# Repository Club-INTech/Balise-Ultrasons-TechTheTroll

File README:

Ceci est le dépôt de la balise de l'équipe TechTheTroll, conçue par Sylvain

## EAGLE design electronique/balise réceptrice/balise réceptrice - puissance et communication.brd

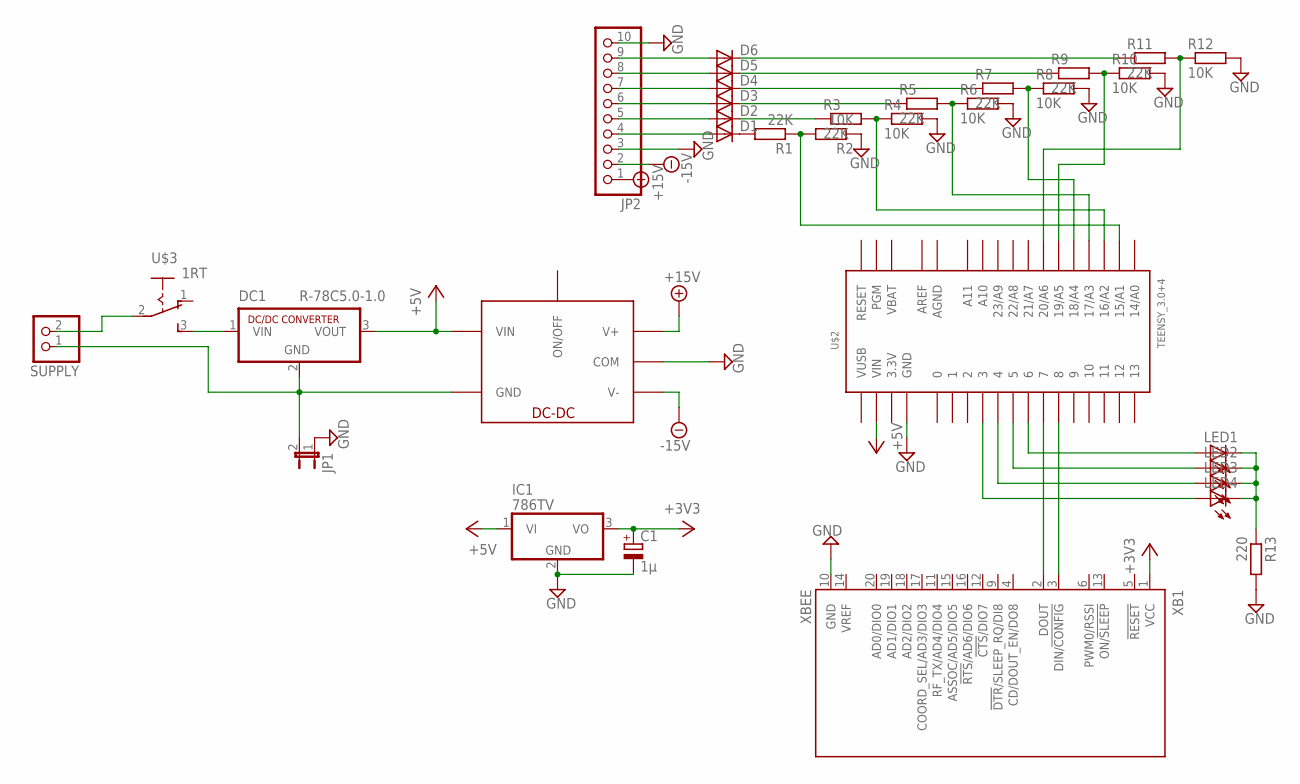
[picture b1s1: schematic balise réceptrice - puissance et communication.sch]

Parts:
C1: 1µ; E2,5-6E
D1, D2, D3, D4, D5, D6: DIODE-D-2.5; D-2.5
DC1: R-78C5.0-1.0; SIP3
IC1: 786TV; TO220V
JP1: JP1E; JP1
JP2: PINHD-1X10; 1X10
LED1, LED2, LED3, LED4: LED3MM
R1, R3, R5, R7, R9, R11: 22K; 0204/7
R2, R4, R6, R8, R10, R12: 10K; 0207/2V
R13: 220; 0204/7
SUPPLY: PINHD-1X2; 1X02
U$1: TMR-6-0523; 7SIL
U$2: TEENSY_3.0+4
U$3: 1RT
XB1: XBEE

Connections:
3.3V: U$2.3.3V, U$2.3.3V1 (3.3V)
+3V3: C1.+, IC1.3 (VO), XB1.1 (VCC)
+5V: DC1.3 (VOUT), IC1.1 (VI), U$1.VCC (VIN), U$2.VIN
+15V: JP2.1, U$1.+V (V+)
-15V: JP2.2, U$1.-V (V-)
AGND: U$2.AGND
AREF: U$2.AREF
GND: C1.-, IC1.2 (GND), JP1.1, JP2.3, JP2.10, R2.1, R4.2, R6.2, R8.2, R10.2, R12.2, R13.2, U$1.COM, U$2.GND, U$2.GND1 (GND), XB1.10 (GND)
unnamed: DC1.2 (GND), JP1.2, SUPPLY.1, U$1.GND
unnamed: D1.A, JP2.4
unnamed: U$2.7, XB1.2 (DOUT)
unnamed: U$2.8, XB1.3 (DIN/!CONFIG)
unnamed: D2.A, JP2.5
unnamed: D3.A, JP2.6
unnamed: D4.A, JP2.7
unnamed: D5.A, JP2.8
unnamed: D6.A, JP2.9
unnamed: R1.1, R2.2, U$2.15/A1
unnamed: D1.C, R1.2
unnamed: D2.C, R3.1
unnamed: R3.2, R4.1, U$2.16/A2
unnamed: D3.C, R5.1
unnamed: R5.2, R6.1, U$2.17/A3
unnamed: D4.C, R7.1
unnamed: R7.2, R8.1, U$2.18/A4
unnamed: D5.C, R9.1
unnamed: R9.2, R10.1, U$2.19/A5
unnamed: D6.C, R11.1
unnamed: R11.2, R12.1, U$2.20/A6
unnamed: DC1.1 (VIN), U$3.3 (S)
unnamed: LED1.A, U$2.6
unnamed: LED2.A, U$2.5
unnamed: LED3.A, U$2.4
unnamed: LED4.A, U$2.3
unnamed: LED1.K (C), LED2.K (C), LED3.K (C), LED4.K (C), R13.1
unnamed: SUPPLY.2, U$3.2
VBAT: U$2.VBAT
VUSB: U$2.VUSB

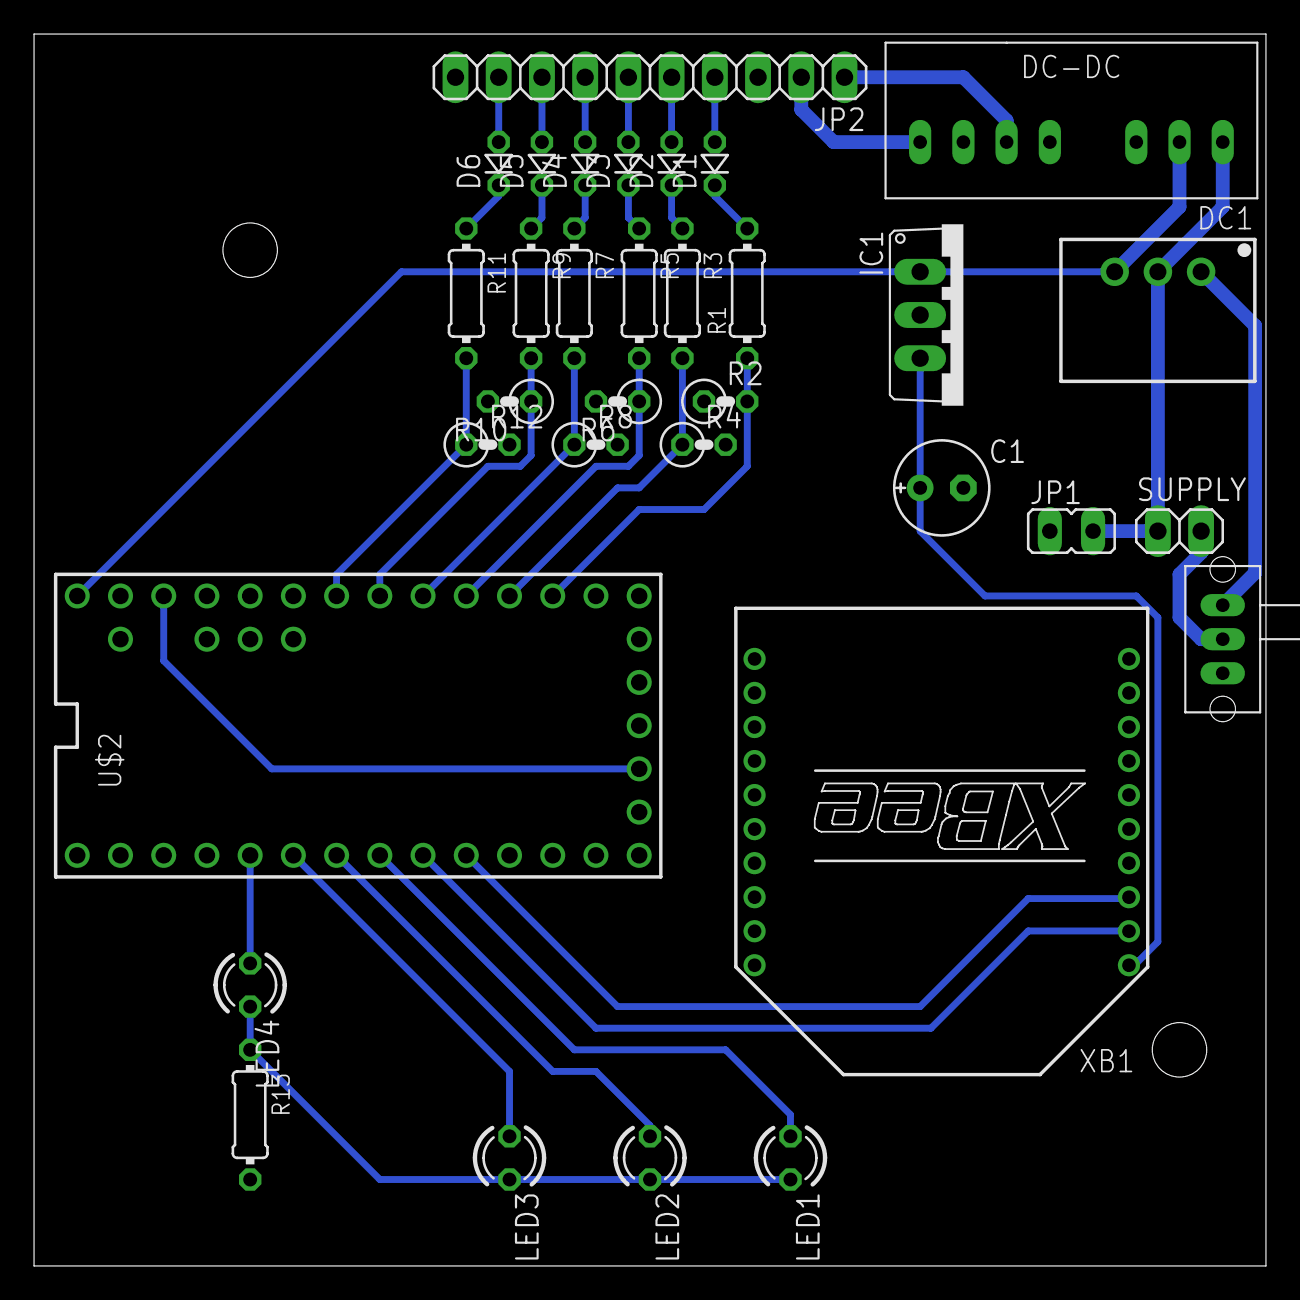
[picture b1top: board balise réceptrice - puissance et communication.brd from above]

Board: 2 copper layers, 72.4 x 72.4 mm, 33 parts (0 on the bottom side), 34 nets.

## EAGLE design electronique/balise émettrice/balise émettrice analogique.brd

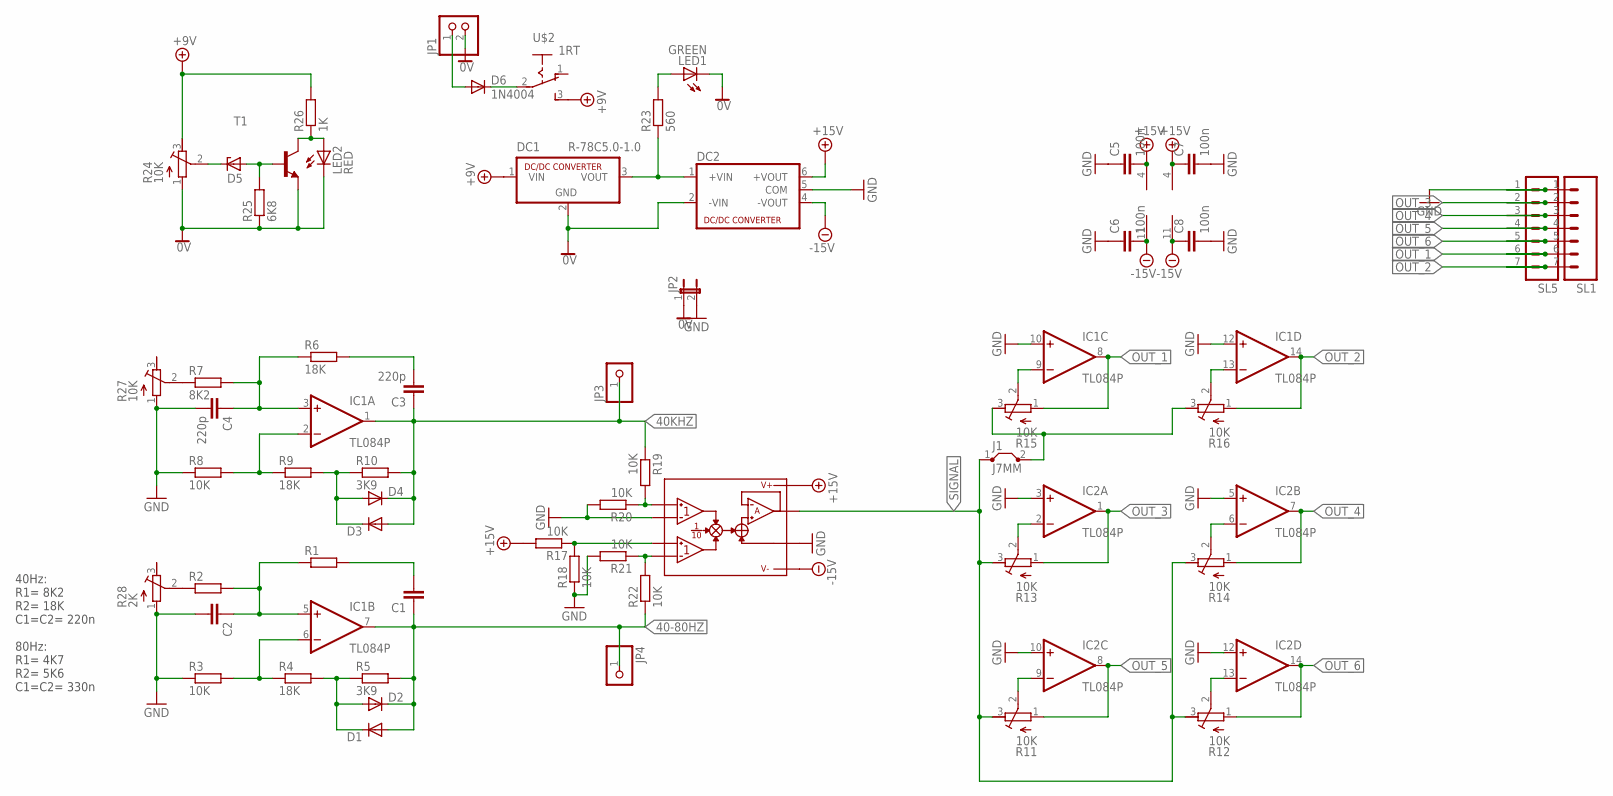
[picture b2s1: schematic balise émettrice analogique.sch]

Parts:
C1, C2: C-EU075-032X103; C075-032X103
C3, C4: 220p; C075-032X103; MPN EEE1EA220SP
C5, C6, C7, C8: 100n; C050-024X044
D1, D2, D3, D4: DIODE-D-2.5; D-2.5
D5: ZENER-DIODEZD-2.5; ZDIO-2.5
D6: 1N4004; DO41-10
DC1: R-78C5.0-1.0; SIP3
DC2: NMA; MPN NMA1205DC
IC1, IC2: TL084P; DIL14
J1: J7MM; 07
JP1: PINHD-1X2; 1X02
JP2: JP1E; JP1
JP3, JP4: PINHD-1X1; 1X01
LED1: GREEN; Q62902-B155
LED2: RED; Q62902-B155
R1: R-EU_0207/2V; 0207/2V
R2: R-EU_0204/7; 0204/7
R3, R8, R17, R18, R19, R20, R21, R22: 10K; 0207/2V
R4, R6, R9: 18K; 0207/2V
R5, R10: 3K9; 0207/2V
R7: 8K2; 0207/2V
R11, R12, R13, R14, R15, R16, R24, R27: 10K; RTRIM3339P
R23: 560; 0204/7
R25: 6K8; 0207/2V
R26: 1K; 0207/2V
R28: 2K; RTRIM3339P
SL1, SL5: M07; 07P
T1: 2N5400-NPN-TO92-CBE; TO92-CBE
U$1: AD633JN; DIL08
U$2: 1RT

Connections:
0V: DC1.2 (GND), DC2.2 (-VIN), JP1.2, JP2.1, LED1.K (C), LED2.K (C), R24.1 (E), R25.1, T1.E
40-80HZ: C1.1, D1.A, D2.C, IC1.7 (OUT), JP4.1, R5.2, R22.1
40KHZ: C3.1, D3.A, D4.C, IC1.1 (OUT), JP3.1, R10.2, R19.1
+9V: DC1.1 (VIN), R24.3 (A), R26.2, U$2.3 (S)
+15V: C5.2, C7.1, DC2.6 (+VOUT), IC1.4 (V+), IC2.4 (V+), R17.2, U$1.8 (+V)
-15V: C6.2, C8.1, DC2.4 (-VOUT), IC1.11 (V-), IC2.11 (V-), U$1.5 (-V)
GND: C2.2, C4.2, C5.1, C6.1, C7.2, C8.2, DC2.5 (COM), IC1.10 (+IN), IC1.12 (+IN), IC2.3 (+IN), IC2.5 (+IN), IC2.10 (+IN), IC2.12 (+IN), JP2.2, R3.1, R8.1, R18.1, R20.2, R21.2, R27.1 (E), R28.1 (E), SL1.1, SL5.1, U$1.2 (X2), U$1.6 (Z)
unnamed: IC1.6 (-IN), R3.2, R4.1
unnamed: D1.C, D2.A, R4.2, R5.1
unnamed: IC2.9 (-IN), R11.2 (S)
unnamed: C1.2, R1.2
unnamed: C2.1, IC1.5 (+IN), R1.1, R2.2
unnamed: IC1.2 (-IN), R8.2, R9.1
unnamed: D3.C, D4.A, R9.2, R10.1
unnamed: R17.1, R18.2, U$1.3 (Y1)
unnamed: C3.2, R6.2
unnamed: C4.1, IC1.3 (+IN), R6.1, R7.2
unnamed: DC1.3 (VOUT), DC2.1 (+VIN), R23.1
unnamed: IC2.13 (-IN), R12.2 (S)
unnamed: R19.2, R20.1, U$1.1 (X1)
unnamed: LED1.A, R23.2
unnamed: IC2.2 (-IN), R13.2 (S)
unnamed: R21.1, R22.2, U$1.4 (Y2)
unnamed: D5.C, R24.2 (S)
unnamed: IC2.6 (-IN), R14.2 (S)
unnamed: D5.A, R25.2, T1.B
unnamed: D6.A, JP1.1
unnamed: IC1.9 (-IN), R15.2 (S)
unnamed: LED2.A, R26.1, T1.C
unnamed: D6.C, U$2.2
unnamed: IC1.13 (-IN), R16.2 (S)
unnamed: J1.2, R15.3 (A), R16.3 (A)
unnamed: R7.1, R27.2 (S)
unnamed: R2.1, R28.2 (S)
OUT_1: IC1.8 (OUT), R15.1 (E), SL1.6, SL5.6
OUT_2: IC1.14 (OUT), R16.1 (E), SL1.7, SL5.7
OUT_3: IC2.1 (OUT), R13.1 (E), SL1.2, SL5.2
OUT_4: IC2.7 (OUT), R14.1 (E), SL1.3, SL5.3
OUT_5: IC2.8 (OUT), R11.1 (E), SL1.4, SL5.4
OUT_6: IC2.14 (OUT), R12.1 (E), SL1.5, SL5.5
SIGNAL: J1.1, R11.3 (A), R12.3 (A), R13.3 (A), R14.3 (A), U$1.7 (W)

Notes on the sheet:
40Hz: R1= 8K2 R2= 18K C1=C2= 220n 80Hz: R1= 4K7 R2= 5K6 C1=C2= 330n

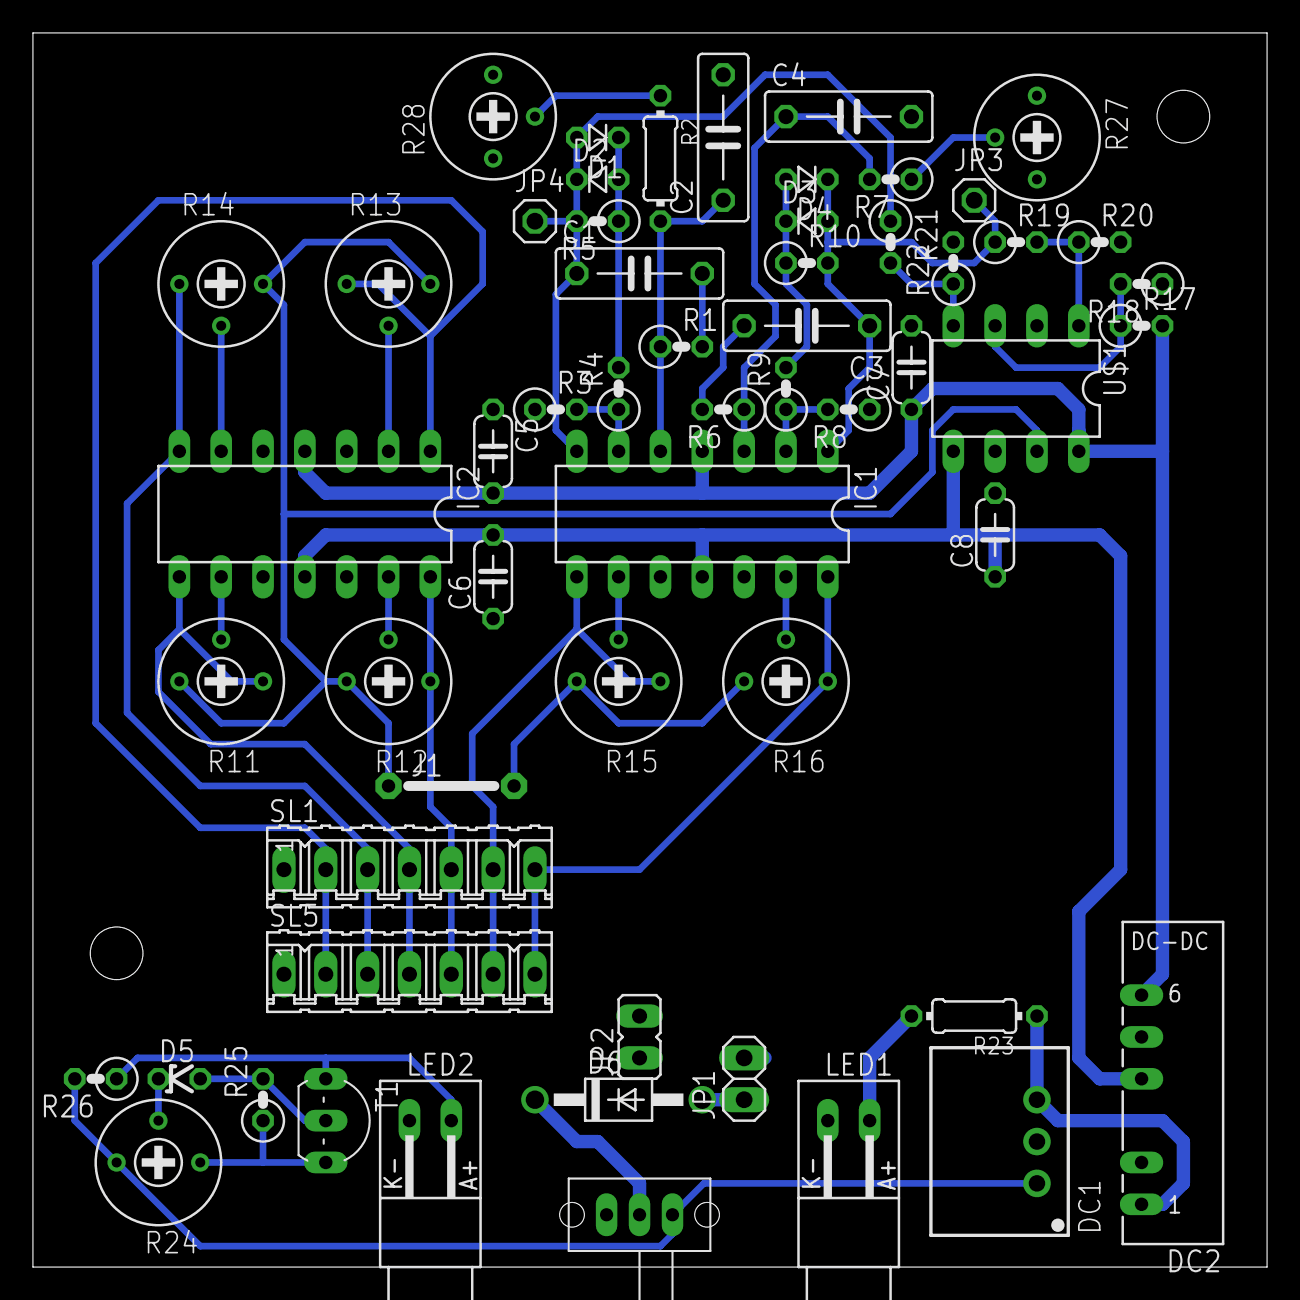
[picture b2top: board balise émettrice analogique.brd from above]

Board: 2 copper layers, 74.9 x 74.9 mm, 58 parts (0 on the bottom side), 41 nets.

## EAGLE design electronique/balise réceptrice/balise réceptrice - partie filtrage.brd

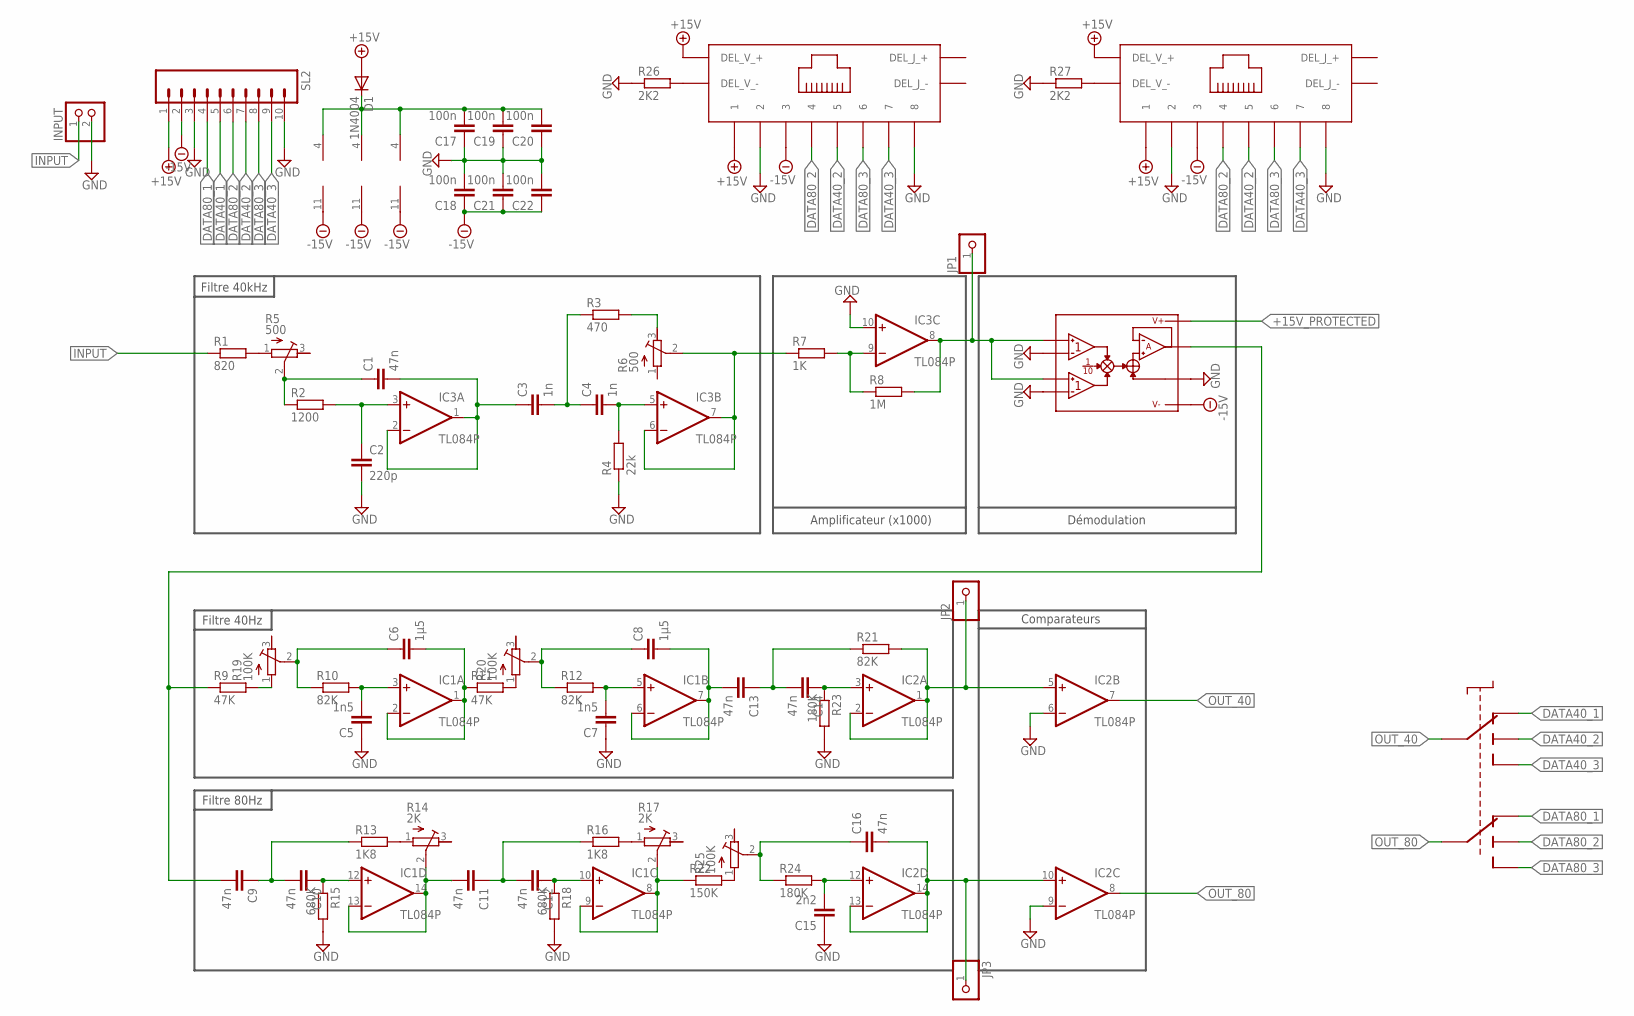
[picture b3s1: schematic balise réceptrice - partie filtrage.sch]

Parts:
C1, C9, C10, C11, C12, C13, C14, C16: 47n; C050-024X044
C2: 220p; C050-024X044; MPN RR1220P-104-B-T5
C3, C4: 1n; C050-024X044
C5, C7: 1n5; C050-024X044
C6, C8: 1µ5; C150-091X182
C15: 2n2; C050-024X044
C17, C18, C19, C20, C21, C22: 100n; C050-024X044
D1: 1N4004; DO41-10
IC1, IC2, IC3: TL084P; DIL14
INPUT: PINHD-1X2; 1X02
JP1, JP2, JP3: PINHD-1X1; 1X01
R1: 820; 0207/2V
R2: 1200; 0207/2V
R3: 470; 0207/2V
R4: 22k; 0207/2V
R5, R6: 500; RTRIM3339P
R7: 1K; 0204/7
R8: 1M; 0204/7
R9: 47K; 0204/7
R10: 82K; 0204/7
R11: 47K; 0207/2V
R12, R21: 82K; 0207/2V
R13, R16: 1K8; 0207/2V
R14, R17: 2K; RTRIM3339P
R15, R18: 680K; 0207/2V
R19, R20, R25: 100K; RTRIM3339P
R22: 150K; 0207/2V
R23, R24: 180K; 0207/2V
R26, R27: 2K2; 0207/2V
SL2: M10; 10P
U$1: AD633JN; DIL08
U$2, U$3: RJ45_FEMELLE
U$4: SWITCH_DP3T_SP112; SWITCH_SP112

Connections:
+15V: D1.A, SL2.1, U$2.1, U$2.DEL_V_+, U$3.1, U$3.DEL_V_+
+15V_PROTECTED: C17.2, C19.2, C20.2, D1.C, IC1.4 (V+), IC2.4 (V+), IC3.4 (V+), U$1.8 (+V)
-15V: C18.1, C21.1, C22.1, IC1.11 (V-), IC2.11 (V-), IC3.11 (V-), SL2.2, U$1.5 (-V), U$2.3, U$3.3
DATA40_1: SL2.5, U$4.1A
DATA40_2: SL2.7, U$2.5, U$3.5, U$4.1B
DATA40_3: SL2.9, U$2.7, U$3.7, U$4.1C
DATA80_1: SL2.4, U$4.2A
DATA80_2: SL2.6, U$2.4, U$3.4, U$4.2B
DATA80_3: SL2.8, U$2.6, U$3.6, U$4.2C
GND: C2.2, C5.1, C7.1, C15.1, C17.1, C18.2, C19.1, C20.1, C21.2, C22.2, IC2.6 (-IN), IC2.9 (-IN), IC3.10 (+IN), INPUT.2, R4.1, R15.2, R18.2, R23.2, R26.1, R27.1, SL2.3, SL2.10, U$1.2 (X2), U$1.4 (Y2), U$1.6 (Z), U$2.2, U$2.8, U$3.2, U$3.8
INPUT: INPUT.1, R1.1
unnamed: C2.1, IC3.3 (+IN), R2.2
unnamed: IC3.9 (-IN), R7.2, R8.1
unnamed: IC3.8 (OUT), JP1.1, R8.2, U$1.1 (X1), U$1.3 (Y1)
unnamed: R1.2, R5.1 (E)
unnamed: C1.1, R2.1, R5.2 (S)
unnamed: C1.2, C3.1, IC3.1 (OUT), IC3.2 (-IN)
unnamed: C3.2, C4.1, R3.1
unnamed: C4.2, IC3.5 (+IN), R4.2
unnamed: IC3.6 (-IN), IC3.7 (OUT), R6.2 (S), R7.1
unnamed: R3.2, R6.3 (A)
unnamed: R26.2, U$2.DEL_V_-
unnamed: C6.1, R10.1, R19.2 (S)
unnamed: C5.2, IC1.3 (+IN), R10.2
unnamed: C6.2, IC1.1 (OUT), IC1.2 (-IN), R11.1
unnamed: R13.2, R14.1 (E)
unnamed: C8.1, R12.1, R20.2 (S)
unnamed: C7.2, IC1.5 (+IN), R12.2
unnamed: C8.2, C13.2, IC1.6 (-IN), IC1.7 (OUT)
unnamed: C9.1, C10.2, R13.1
unnamed: C11.2, IC1.13 (-IN), IC1.14 (OUT), R14.2 (S)
unnamed: C10.1, IC1.12 (+IN), R15.1
unnamed: R16.2, R17.1 (E)
unnamed: C11.1, C12.2, R16.1
unnamed: IC1.8 (OUT), IC1.9 (-IN), R17.2 (S), R22.1
unnamed: C12.1, IC1.10 (+IN), R18.1
unnamed: C9.2, R9.1, U$1.7 (W)
unnamed: R9.2, R19.1 (E)
unnamed: R11.2, R20.1 (E)
unnamed: C16.1, R24.1, R25.2 (S)
unnamed: C15.2, IC2.12 (+IN), R24.2
unnamed: C13.1, C14.2, R21.1
unnamed: IC2.1 (OUT), IC2.2 (-IN), IC2.5 (+IN), JP2.1, R21.2
unnamed: C14.1, IC2.3 (+IN), R23.1
unnamed: C16.2, IC2.10 (+IN), IC2.13 (-IN), IC2.14 (OUT), JP3.1
unnamed: R22.2, R25.1 (E)
unnamed: R27.2, U$3.DEL_V_-
OUT_40: IC2.7 (OUT), U$4.COM_1 (COM1)
OUT_80: IC2.8 (OUT), U$4.COM_2 (COM2)

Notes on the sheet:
Filtre 40Hz
Filtre 80Hz
Comparateurs
Filtre 40kHz
Amplificateur (x1000)
Démodulation

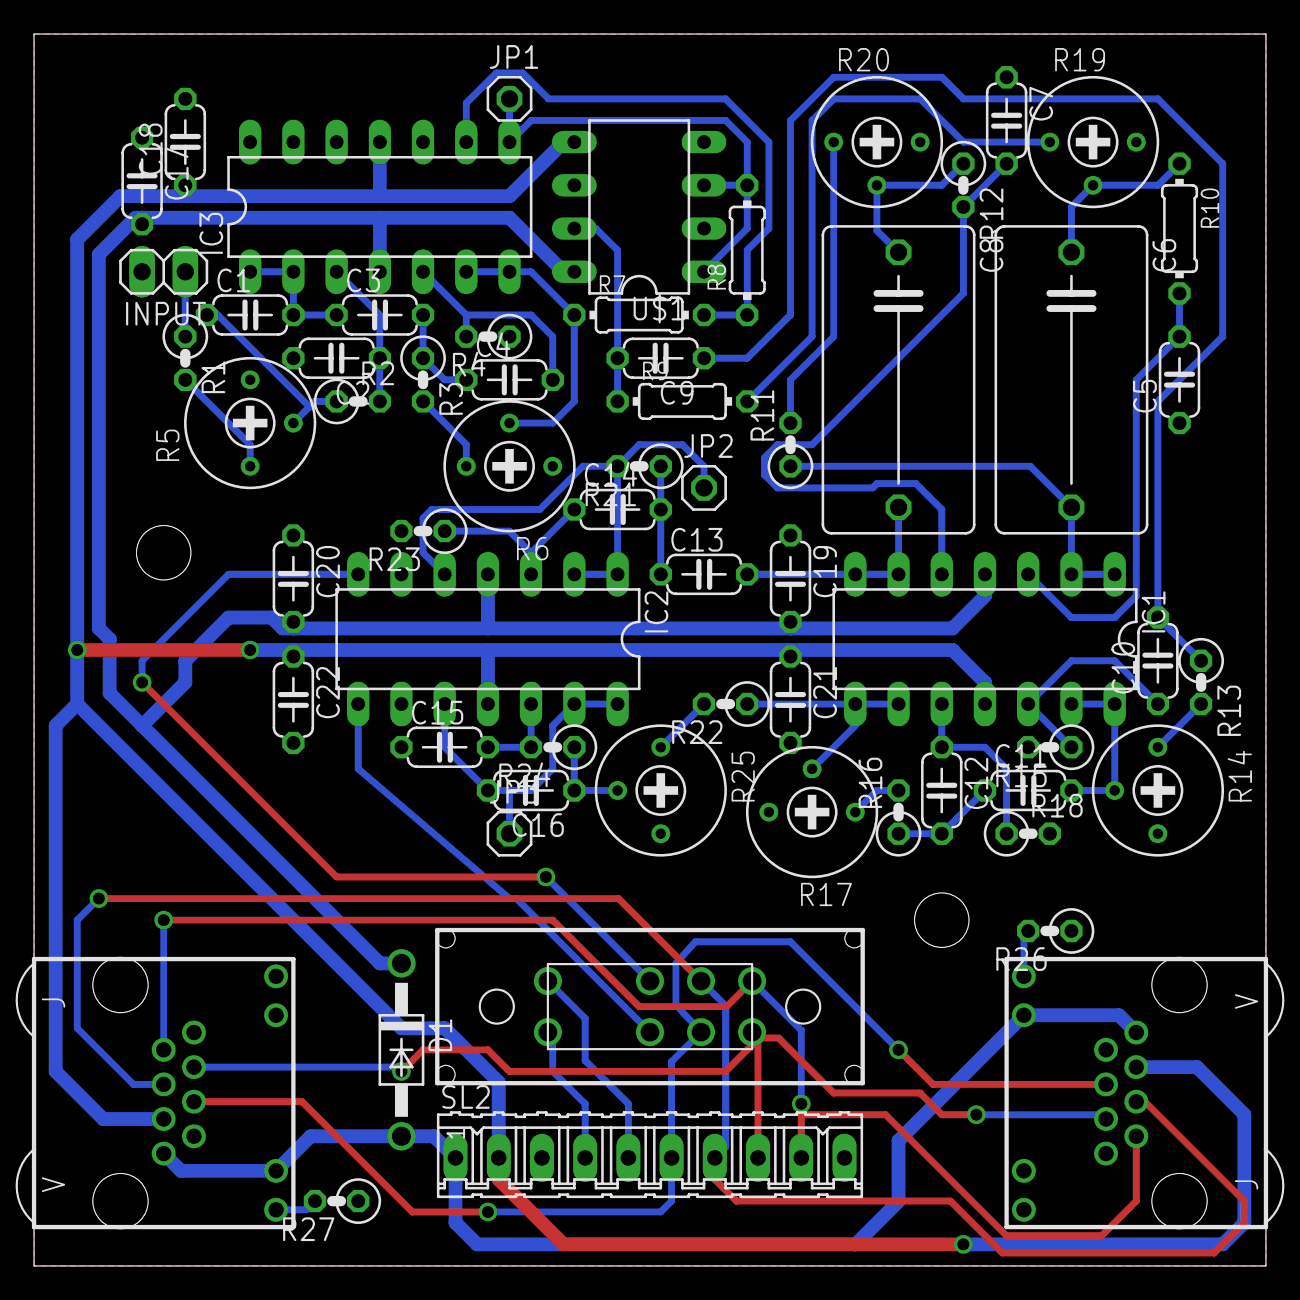
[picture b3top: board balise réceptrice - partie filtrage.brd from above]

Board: 2 copper layers, 72.4 x 72.4 mm, 62 parts (0 on the bottom side), 49 nets.

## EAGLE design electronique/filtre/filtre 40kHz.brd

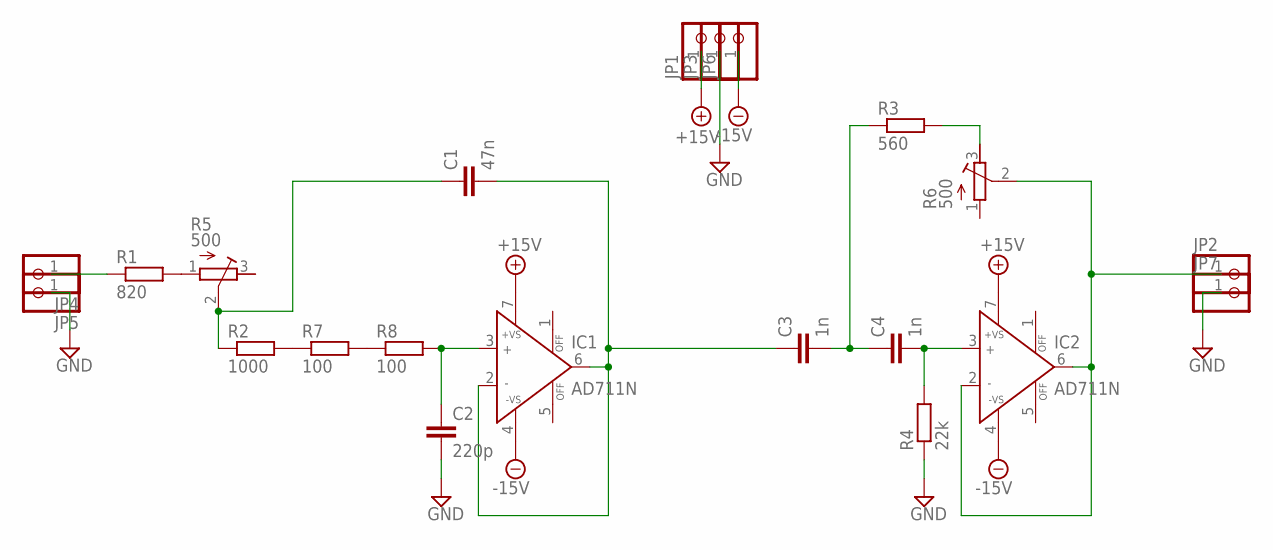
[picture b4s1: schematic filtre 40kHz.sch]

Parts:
C1: 47n; C050-024X044
C2: 220p; C050-024X044
C3: 1n; C075-032X103
C4: 1n; C050-024X044
IC1, IC2: AD711N; DIL08
JP1, JP2, JP3, JP4, JP5, JP6, JP7: PINHD-1X1; 1X01
R1: 820; 0204/7
R2: 1000; 0204/7
R3: 560; 0204/7
R4: 22k; 0204/7
R5, R6: 500; RTRIM3339P
R7, R8: 100; 0207/2V

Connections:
+15V: IC1.7 (+VS), IC2.7 (+VS), JP1.1
-15V: IC1.4 (-VS), IC2.4 (-VS), JP6.1
GND: C2.2, JP3.1, JP5.1, JP7.1, R4.1
unnamed: C2.1, IC1.3 (IN+), R8.2
unnamed: R2.2, R7.1
unnamed: R7.2, R8.1
unnamed: R1.2, R5.1 (E)
unnamed: C1.1, R2.1, R5.2 (S)
unnamed: C1.2, C3.1, IC1.2 (IN-), IC1.6 (OUT)
unnamed: C3.2, C4.1, R3.1
unnamed: C4.2, IC2.3 (IN+), R4.2
unnamed: IC2.2 (IN-), IC2.6 (OUT), JP2.1, R6.2 (S)
unnamed: R3.2, R6.3 (A)
unnamed: JP4.1, R1.1

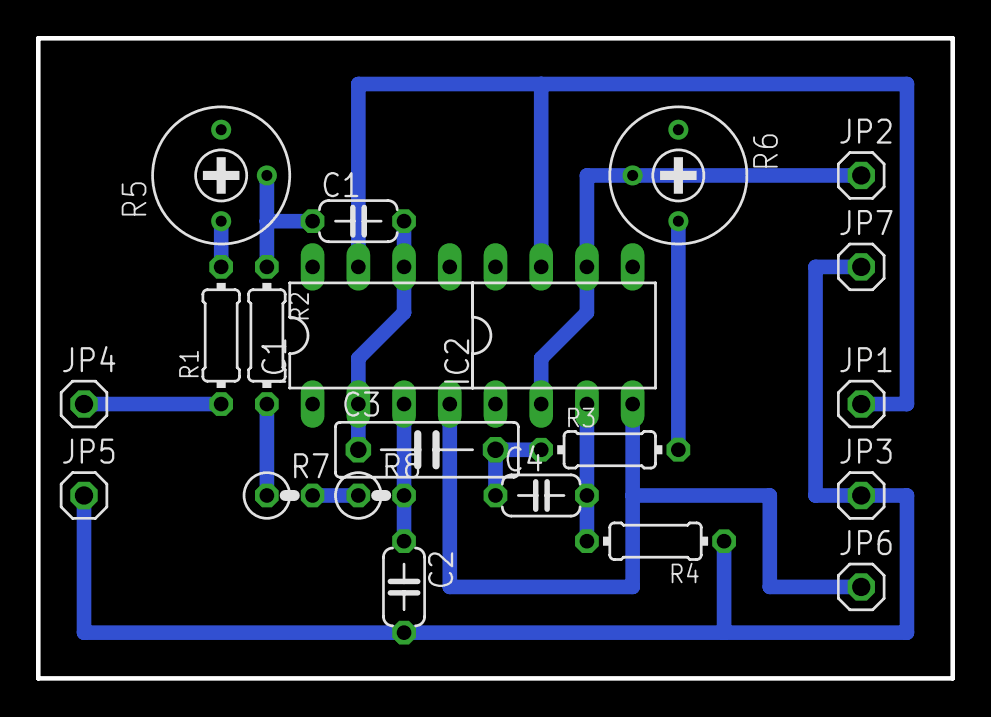
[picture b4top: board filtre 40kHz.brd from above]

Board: 2 copper layers, 50.8 x 35.6 mm, 21 parts (0 on the bottom side), 14 nets.

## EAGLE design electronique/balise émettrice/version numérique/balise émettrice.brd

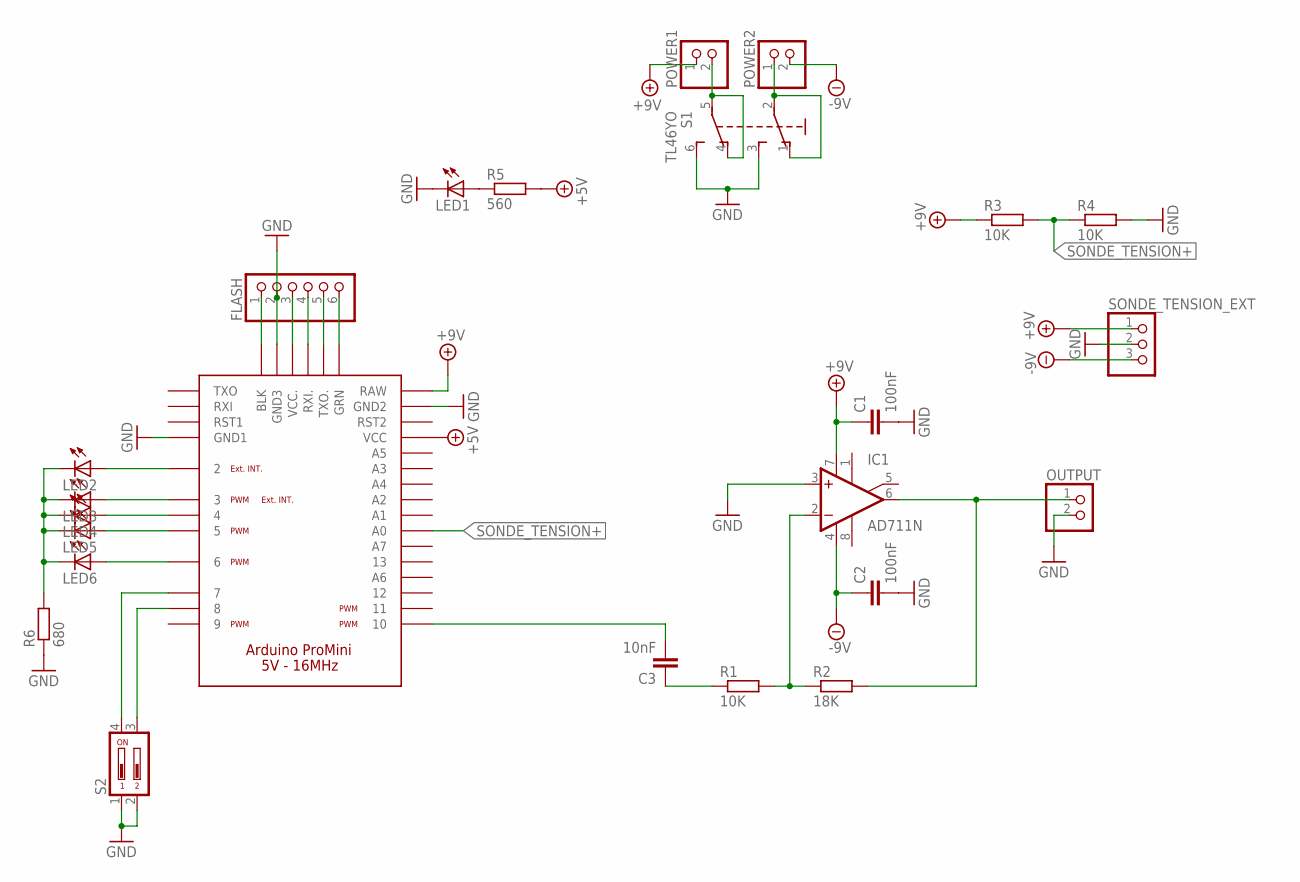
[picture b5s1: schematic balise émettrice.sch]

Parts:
C1, C2: 100nF; C050-024X044
C3: 10nF; C050-024X044
FLASH: PINHD-1X6/90; 1X06/90
IC1: AD711N; DIL08
LED1: LEDB155; Q62902-B155
LED2, LED3, LED4, LED5, LED6: LED3MM
OUTPUT: PINHD-1X2; 1X02
POWER1, POWER2: PINHD-1X2; 1X02
R1, R3, R4: 10K; 0204/7
R2: 18K; 0204/7
R5: 560; 0207/12
R6: 680; 0204/7
S1: TL46YO; TL4XYO
S2: DA02; DA-02
SONDE_TENSION_EXT: PINHD-1X3; 1X03
U$1: ARDUINO_PRO_MINI

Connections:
+5V: R5.2, U$1.VCC1 (VCC)
+9V: C1.1, IC1.7 (V+), POWER1.1, R3.1, SONDE_TENSION_EXT.1, U$1.RAW
-9V: C2.1, IC1.4 (V-), POWER2.2, SONDE_TENSION_EXT.3
GND: C1.2, C2.2, FLASH.2, IC1.3 (+IN), LED1.K (C), OUTPUT.2, R4.2, R6.1, S1.3 (S), S1.6 (S1), S2.1, S2.2, SONDE_TENSION_EXT.2, U$1.GND1, U$1.GND2, U$1.GND3
unnamed: FLASH.1, U$1.BLK
unnamed: IC1.6 (OUT), OUTPUT.1, R2.2
unnamed: IC1.2 (-IN), R1.2, R2.1
unnamed: LED1.A, R5.1
unnamed: FLASH.3, U$1.VCC2 (VCC.)
unnamed: FLASH.4, U$1.RXI2 (RXI.)
unnamed: FLASH.5, U$1.TXO2 (TXO.)
unnamed: FLASH.6, U$1.GRN
unnamed: C3.1, R1.1
unnamed: LED2.A, U$1.2
unnamed: LED3.A, U$1.3
unnamed: LED4.A, U$1.4
unnamed: LED5.A, U$1.5
unnamed: LED6.A, U$1.6
unnamed: LED2.K (C), LED3.K (C), LED4.K (C), LED5.K (C), LED6.K (C), R6.2
unnamed: POWER1.2, S1.4 (O1), S1.5 (P1)
unnamed: POWER2.1, S1.1 (O), S1.2
unnamed: S2.4, U$1.7
unnamed: S2.3, U$1.8
unnamed: C3.2, U$1.10
SONDE_TENSION+: R3.2, R4.1, U$1.A0

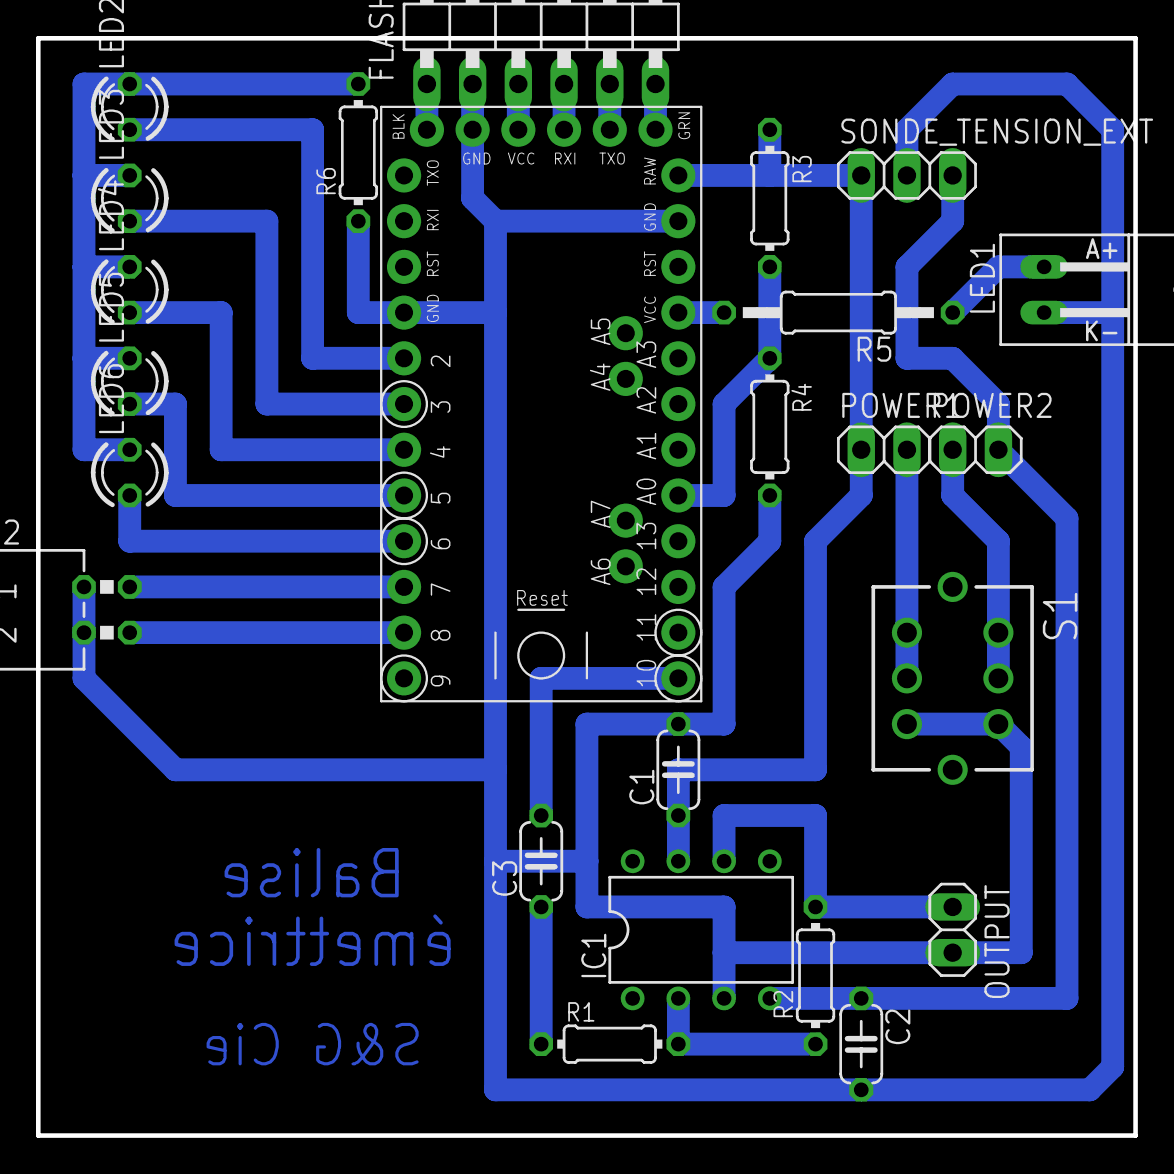
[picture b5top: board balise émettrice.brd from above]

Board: 2 copper layers, 61.0 x 61.0 mm, 24 parts (0 on the bottom side), 25 nets.

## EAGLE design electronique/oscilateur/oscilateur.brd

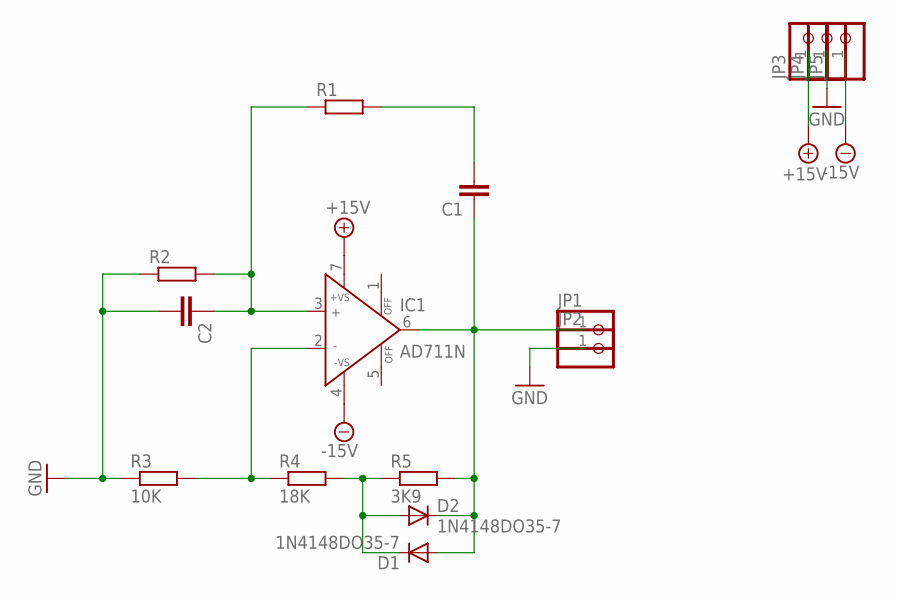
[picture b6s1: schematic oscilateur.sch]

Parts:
C1, C2: C-EU075-032X103; C075-032X103
D1, D2: 1N4148DO35-7; DO35-7
IC1: AD711N; DIL08
JP1, JP2, JP3, JP4, JP5: PINHD-1X1; 1X01
R1, R2: R-EU_0204/7; 0204/7
R3: 10K; 0204/7
R4: 18K; 0204/7
R5: 3K9; 0204/7

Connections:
+15V: IC1.7 (+VS), JP3.1
-15V: IC1.4 (-VS), JP5.1
GND: C2.2, JP2.1, JP4.1, R2.1, R3.1
unnamed: IC1.2 (IN-), R3.2, R4.1
unnamed: D1.C, D2.A, R4.2, R5.1
unnamed: C1.1, D1.A, D2.C, IC1.6 (OUT), JP1.1, R5.2
unnamed: C1.2, R1.2
unnamed: C2.1, IC1.3 (IN+), R1.1, R2.2

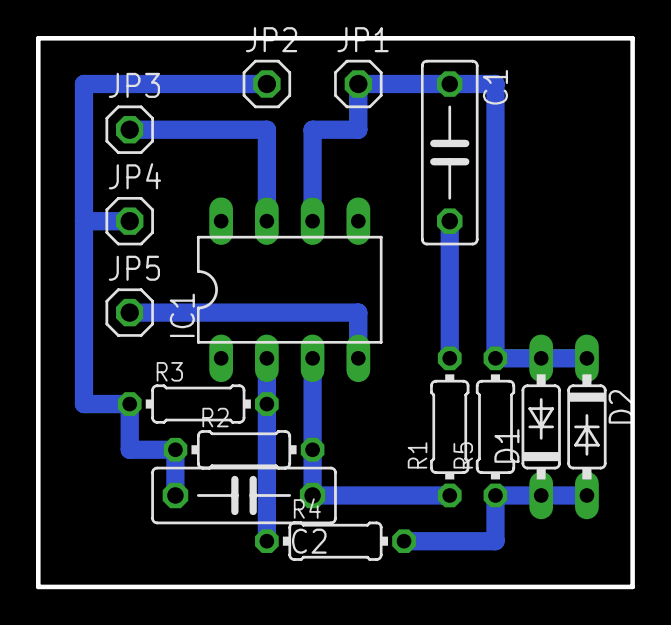
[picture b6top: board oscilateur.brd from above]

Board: 2 copper layers, 33.0 x 30.5 mm, 15 parts (0 on the bottom side), 8 nets.

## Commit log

2015-06-25 premier commit
2015-06-25 ajout du gitignore
2015-06-25 nettoyage des fichiers qui se revelent penibles a versionner...
2015-06-25 fix the fuck up
2015-06-25 Revert "fix the fuck up"
    This reverts commit 9a87e45b5d8bd9265cc6f213deac9424c01c1d64.
2015-06-25 Revert "nettoyage des fichiers qui se revelent penibles a versionner..."
    This reverts commit 4f999430c8d0b5a707e8b82945da2f093fba8c61.
2015-06-25 Revert "Revert "nettoyage des fichiers qui se revelent penibles a versionner...""
    This reverts commit 346a37e5f3388ba9037312f81a1cfd123524a31b.
2015-06-25 Revert "Revert "fix the fuck up""
    This reverts commit ae1d21c6338c15d75db3a7bee004fff2f4440deb.
2015-06-25 Revert "Revert "fix the fuck up""
    This reverts commit ef9bef084db1ce953202a2d8b7460675332a287e.
2015-06-25 Revert "Revert "Revert "fix the fuck up"""
    This reverts commit bf3d6eea3e80966900aa8c178e6fd80a61835c0a.
2015-06-25 Revert "Revert "Revert "nettoyage des fichiers qui se revelent penibles a versionner..."""
    This reverts commit f60757fa0cf28b790f92727b243827b64f0c8f21.
2015-06-25 Revert "Initial commit"
    This reverts commit 3480876f3016d13950a7f84f514ef47d8ee8be21.
2015-06-25 bon, ce coup ci je sais ce que fait git revert. Et c'est bien pourri. Il y a des fichiers un peu lourds que j'ai push et qui sont desormai dans le gitignore, mais il m'est impossible de les supprimer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
2015-06-25 fix gitignore
2015-07-01 circuit balise emission + filtre 80Hz
2015-07-04 maj elec balise emettrice
2015-07-04 ajout modeles 3d balise emettrice
2015-07-06 ajout .stl + maj modeles 3D + maj elec + maj filtrage
2015-07-07 correctif equations des filtres + ajout debut circuit de reception
2015-07-11 maj filtrage + ajout routage balise receptrice, partie filtrage
2015-07-15 derniere carte elec : la puissance et la communication sans fil + maj modele 3D balise receptrice
2015-07-15 .gitattributes
2015-07-16 maj gitignore
2015-07-16 release modele 3D + elec :D
2015-07-16 maj balise emettrice : ajout de la DEL de debug + interrupteur dans le modele 3D
2015-07-16 ajout des .stl
2015-08-15 maj mineure elec + ajout doc de l'elec
2015-08-25 3 fois rien
2015-09-23 ajout des fichiers gerber et excellon
2015-10-12 Papiers présentants le filtrage de Kalman adapté au problème
2015-10-16 Je suis le premier ! fonctiosn pour retrouver la position du robot à partir des mesures, un filtrage de Kalman classique et le Unscented
2015-10-27 nie rozumiem (pareil qu'avant)
2015-10-27 ajout de l'encodage, important en Python 2.x
2015-10-27 ajout de l'encodage, algorithme de Kalman Unscented. Fichier non fini
2015-11-11 Le code a été mis sous une forme un peu plus objet.
2015-11-11 Doc pour s'instruire sur le fitrage de Kalman
2015-12-15 ajout des factures, devis, et bilans financiers
2015-12-15 Intégration travail Clément
2015-12-15 ajout de la TVA ^^
2015-12-15 maj liste des composants
2016-02-28 Ajout des mesures faites par Julian pour tester le filtrage
2016-02-28 Amélioration de quelques parties du code. Problème de dimensionnement de vecteurs
2016-03-05 Ajout doc + mise a jour des modeles 3D
2016-03-06 Le filtre est désormais cohérent au niveau des dimensions. Il reste encore des problèmes quand à la cohérence des résultats. Par exemple, la racine carré d'une matrice peut devenir complexe au bout d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
2016-03-06 Un * corrigé en un + et on obtient de meilleurs résultats ! Enfin, tout reste dans le même ordre de grandeur. On peut dire que le programme est débogué, mais pas encore opérationnel : beaucoup de par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
2016-03-11 petite amélioration du papier
2016-03-30 Ajout d'un script qui génère comme on veut des mesures de position d'un robot sur la table de jeu.
2016-03-30 Renommage de fichiers. Ajout d'un script utilisant le générateur de chemin. Test. A ajouter : l'analyse des erreurs.
2016-03-31 Documentation ajoutée. Je passe le code à Monf aussi, il a besoin de mesures et ça peut aider.
2016-04-05 ajout de trajectoires bruités pour des tests
2016-04-13 Séparation du code sur le filtrage et sur les structures de données
2016-04-13 Utilisation de structure.py
2016-04-13 utilisation de structure et ajout d'un terme dans les sommes. L'algo n'est pas encore totalement prêt.
2016-04-13 quelques arrangements
2016-04-25 de meilleures valeurs, mais c'est toujours un peu "nul"
2016-04-27 Filtre de Kalman d'Ivan
2016-04-30 Test de la méthode d'Ivan
2016-04-30 On essaye de trouver les meilleures valeurs pour les matrices de covariance.
2016-05-02 Des avancées ? Pas sûr. Oui, j'aime pas écrire des trucs utiles.
2016-05-10 ajout code Teensy
2016-05-13 maj soft teensy
2016-05-14 Ajout d'un module qui permet de lire les mesures effectuées par Sylvain et reçu sous la forme d'un fichier texte.
2016-05-14 Ajout des données brutes des balises et des données légèrement retouchées
2016-05-15 ajout des données résultats des tests pour Clément, et correction du code bas niveau
2016-05-21 Début du pseudo-code du filtrage de Kalman
2016-05-22 Pseudo-code totalement écrit. Ajout d'une documentation. Modélisation plus précise. Ajout d'une partie sur l'explication sur les notations.
2016-07-21 ajout de mesures
2016-07-22 Create LICENSE
2016-07-22 ajout script python de traitement sommaire des benchmark
2016-07-22 commit pré-merge, gardons la foi.
2016-07-22 gitignore
2016-07-23 Affichage des données
2016-07-23 Lecture de fichier, debug multithreading
2016-07-23 Debug
2016-07-24 Sire, sire, ça marche !
2016-07-25 Points reliés
2016-07-25 Conversion entre deux formats de fichiers
2016-07-25 Output en png
2016-07-25 Affichage des demi-hyperboles
2016-07-25 Correction conversion
2016-07-25 Suppression de la 2e solution
2016-07-25 Ligne de commande + jar
2016-07-25 Conversion des P1, …, P9 en format vanille-chocolat
2016-07-25 Conversion plus robuste par rapport au format d'entrée
2016-07-25 Filtre par médiane
2016-07-26 Triangulation choisit la bonne solution
2016-07-26 Meilleure gestion quand il y a plusieurs trajectoires
2016-07-26 Petit test de sensibilité au bruit
2016-07-26 Séparation du calcul de filtrage et de l'affichage afin de pouvoir s'interfacer avec les filtres python
2016-07-26 Positions brutes de P1 pour tester le Kalman
2016-07-26 test du filtre de Kalman avec des mesures converties analytiquement
2016-07-26 Des entiers pour les positions !!!
2016-07-27 ajout de documentation
2016-07-27 print en ligne
2016-07-28 Mesures avec robot immobile
2016-07-28 La triangulation vérifie la cohérence des données
2016-07-28 ajout des premiers relevés de test
2016-07-28 oups
2016-07-30 Premier test avec ordonnanceur java
2016-07-30 4 more test
2016-07-30 tests avec bon ordre
2016-08-04 Ajout script python pour créer la base de données de mesures permettant de réaliser la fonction inverse.
2016-08-11 More data
